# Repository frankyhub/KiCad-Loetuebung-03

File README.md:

<div align="center">

|[:skull:ISSUE](https://github.com/frankyhub/KiCad-Loetuebung-03/issues?q=is%3Aissue)|[:speech_balloon: Forum /Discussion](https://github.com/frankyhub/KiCad-Loetuebung-03/discussions)|[:grey_question:WiKi](https://github.com/frankyhub/KiCad-Loetuebung-03/wiki)||
|--|--|--|--|
| | | | |
<a href="https://github.com/frankyhub/KiCad-Loetuebung-03/issues">|<a href="https://github.com/frankyhub/KiCad-Loetuebung-03/discussions">|<a href="https://github.com/frankyhub/KiCad-Loetuebung-03/6eleases">||
|| <a href="https://github.com/frankyhub/KiCad-Loetuebung-03/pulse" alt="Activity">| <a href="https://github.com/frankyhub/KiCad-Loetuebung-03/graphs/traffic">  |<a href="https://github.com/frankyhub?tab=stars"> ||

</div>

## BOM

| Anzahl | Bezeichnung | 
| -------- | -------- | 
| 1  |  Platine	  |
|  1 | Batteriehalter	   |
| 1  | CR2032	   |
| 1  |  S1	Micro_Schalter  |
| 1  |  U1 NE555	  |
| 1  |  C1	1	220uF  |
| 1  |  D1	1N4148 |
| 2  | P1, P2 10k   |
| 2  | Q1, Q2 BC548   |
| 1  | R3 560k  |
| 1  | R4 390k   |
| 1  | R5 4k7   |
|  1 |  R6 10R   |
|  10 |  LED rt 3mm  |
| -------- | -------- | 

---

|	               |Löten I  |Löten II 	   |Löten III|
|--|--|--|--|
|1 x Platine		|:white_check_mark:|:white_check_mark:|:white_check_mark:|
|1 x Batteriehalter 9V  |:white_check_mark:|:x:|:x:|
|1 x Batterie 9V        |:white_check_mark:|:x:|:x:|
|1 x Batteriehalter CR2032 |:x:	|:white_check_mark:|:white_check_mark:|
|1 x CR2032		|:x:|:white_check_mark:|:white_check_mark:|
|1 x Schalter		|:x:|:white_check_mark:|:white_check_mark:|
|1 x NE555		|:x:|:white_check_mark:|:white_check_mark:|
|1 x R1	12k		|:x:|:white_check_mark:|:x:|
|1 x R2	16k		|:x:|:white_check_mark:|:x:|
|1 x R3	560k		|:x:|:white_check_mark:|:white_check_mark:|
|1 x R4	390k		|:x:|:white_check_mark:|:white_check_mark:|
|4 x 10k		|:white_check_mark:|:x:|:x:|
|1 x R5	4k7		|:x:|:white_check_mark:|:white_check_mark:|
|4 x 470R		|:white_check_mark:|:x:|:x:|
|1 x R6	10R		|:x:|:white_check_mark:|:white_check_mark:|
|1 x D3	1N4148		|:x:|:white_check_mark:|:white_check_mark:|
|4 x BC548		|:white_check_mark:|:x:|:x:|
|2 x Q1, Q2 BC548	|:x:|:white_check_mark:|:white_check_mark:|
|2 x D1, D2 LED	5mm	|:x:|:white_check_mark:|:x:|
|4 x LED 5mm		|:white_check_mark:|:x:|:x:|
|4 x 100uF		|:white_check_mark:|:x:|:x:|
|1 x C1	47uF		|:x:|:white_check_mark:|:white_check_mark:|
|2 x Trimmer 10k	|:x:|:x:|:white_check_mark:|
|10 x LED 3mm		|:x:|:x:|:white_check_mark:|
|                       |~10,-|~10,-|~12,-| 

---

<div style="position:absolute; left:2cm; ">   
<ol class="breadcrumb" style="border-top: 2px solid black;border-bottom:2px solid black; height: 45px; width: 900px;"> <p align="center"><a href="#oben">nach oben</a></p></ol>
</div>  

---

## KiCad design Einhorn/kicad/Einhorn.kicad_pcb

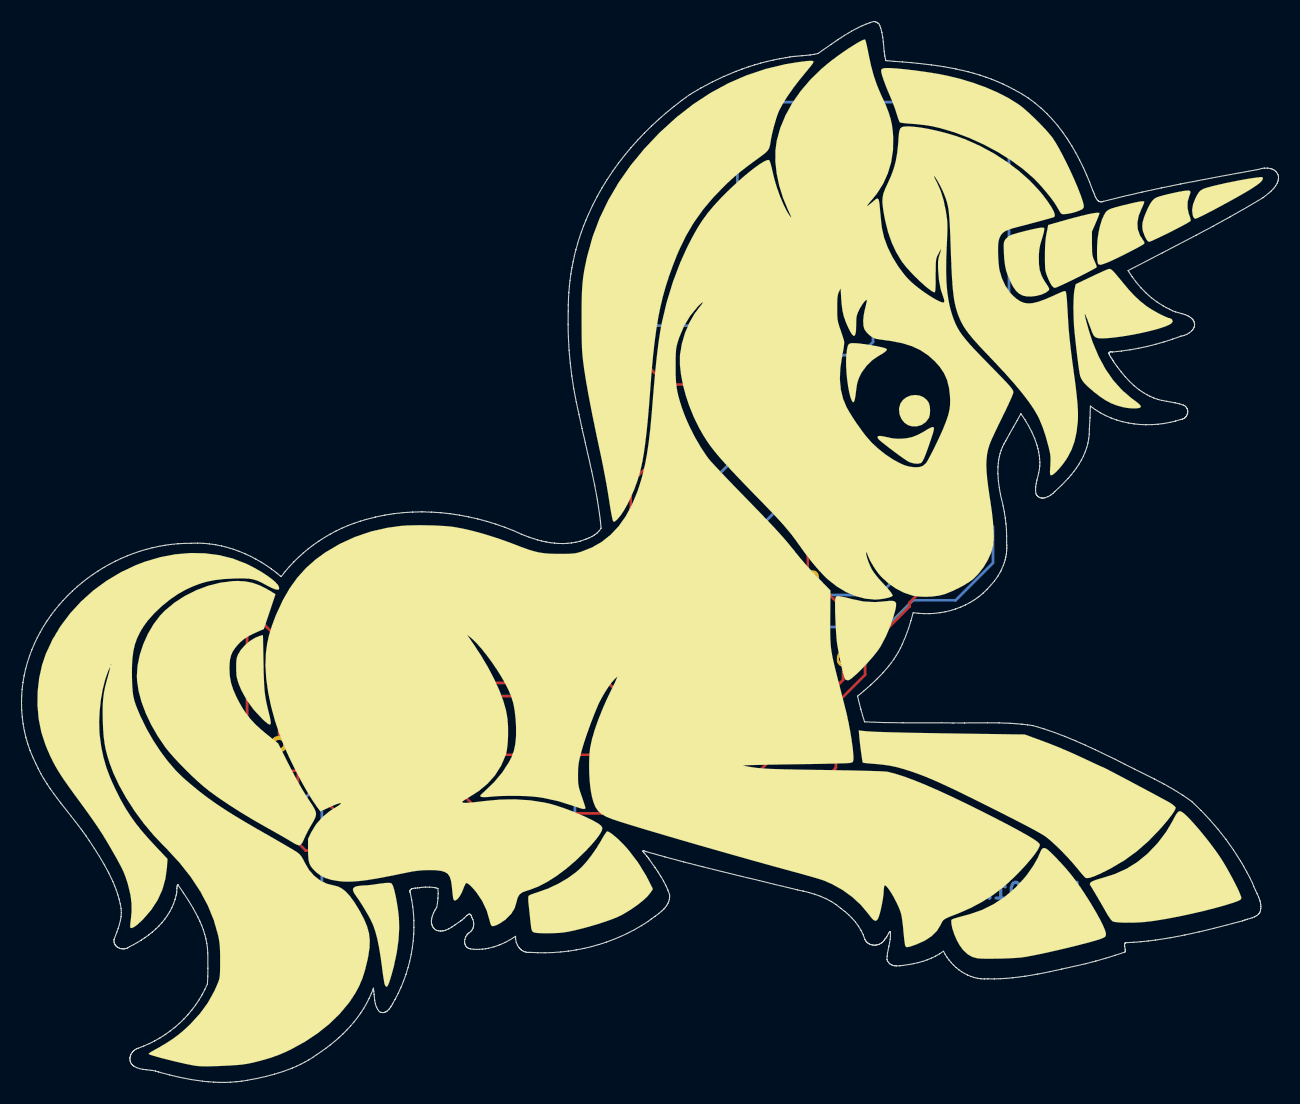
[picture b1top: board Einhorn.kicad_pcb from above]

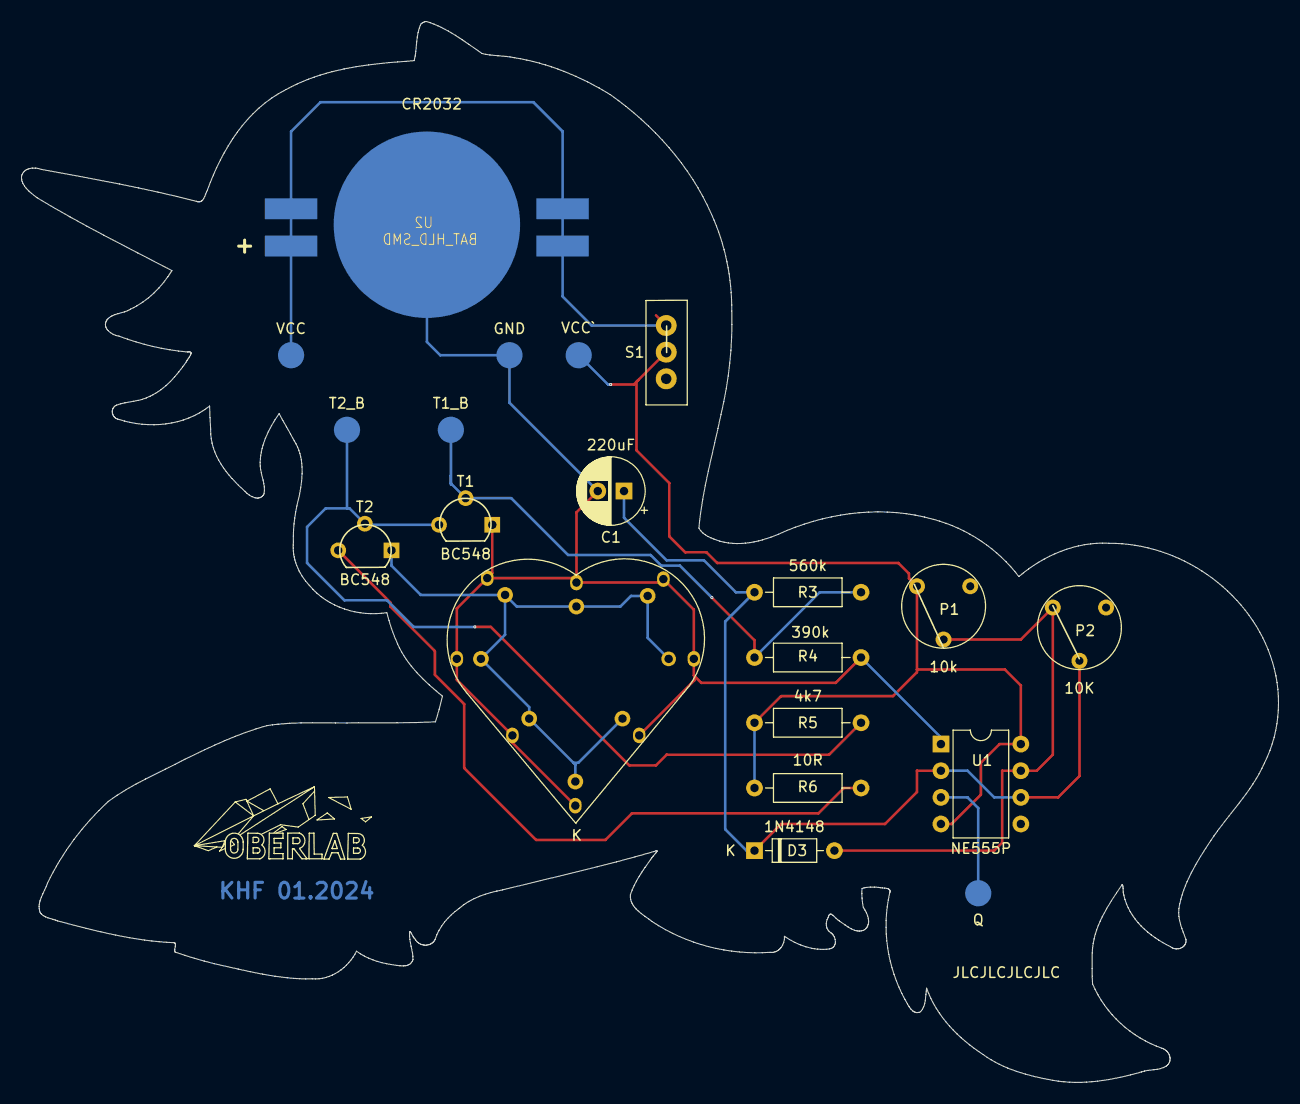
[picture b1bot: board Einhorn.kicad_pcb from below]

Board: 2 copper layers, 119.9 x 101.2 mm, 19 parts (11 on the bottom side), 9 nets.

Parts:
C1: 220uF; CP_Radial_D6.3mm_P2.50mm
D3: 1N4148; D_DO-35_SOD27_P7.62mm_Horizontal
GND: MP_rund
P1: 10k; Mini-Poti
P2: 10K; Mini-Poti
Q: MP_rund
R3: 560k; R_Axial_DIN0207_L6.3mm_D2.5mm_P10.16mm_Horizontal
R4: 390k; R_Axial_DIN0207_L6.3mm_D2.5mm_P10.16mm_Horizontal
R5: 4k7; R_Axial_DIN0207_L6.3mm_D2.5mm_P10.16mm_Horizontal
R6: 10R; R_Axial_DIN0207_L6.3mm_D2.5mm_P10.16mm_Horizontal
S1: Micro_Schalter-; Micro_SchalterKHF
T1, T2: BC548; TO-92L_Wide
T1_B, T2_B: MP_rund
U1: NE555P; DIP-8_W7.62mm
U2: BAT_HLD_SMD; BAT-HLD-SMD-Blech
U3: LED-Herz 8
VCC: MP_rund

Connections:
unnamed: D3.2 (A), P1.3, P2.1, U1.7 (DIS)
unnamed: C1.1, D3.1 (K), P2.3, R3.1, U1.2 (TR), U1.6 (THR)
unnamed: R3.2, R4.1, T1.2, T1_B.1
unnamed: R5.2, T1.3, T2.2, T2_B.1
unnamed: C1.2, GND.1, R4.2, T1.1, U1.1 (GND), U2.2, U3.1 (K)
unnamed: R6.2, T2.3
unnamed: T2.1, U3.2 (A)
unnamed: S1.1 (A), U2.1, VCC.1
unnamed: P1.1, R5.1, R6.1, S1.2 (E), U1.4 (R), U1.8 (VCC)

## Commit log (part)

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2024-02-27 V 01.2024
2024-02-27 V1 01.2024
2024-02-27 BOM Update README.md
2024-04-02 V1.2 02.04.2024
2024-09-22 V 22092024
2024-10-12 V12102024
2025-03-31 V31032025
